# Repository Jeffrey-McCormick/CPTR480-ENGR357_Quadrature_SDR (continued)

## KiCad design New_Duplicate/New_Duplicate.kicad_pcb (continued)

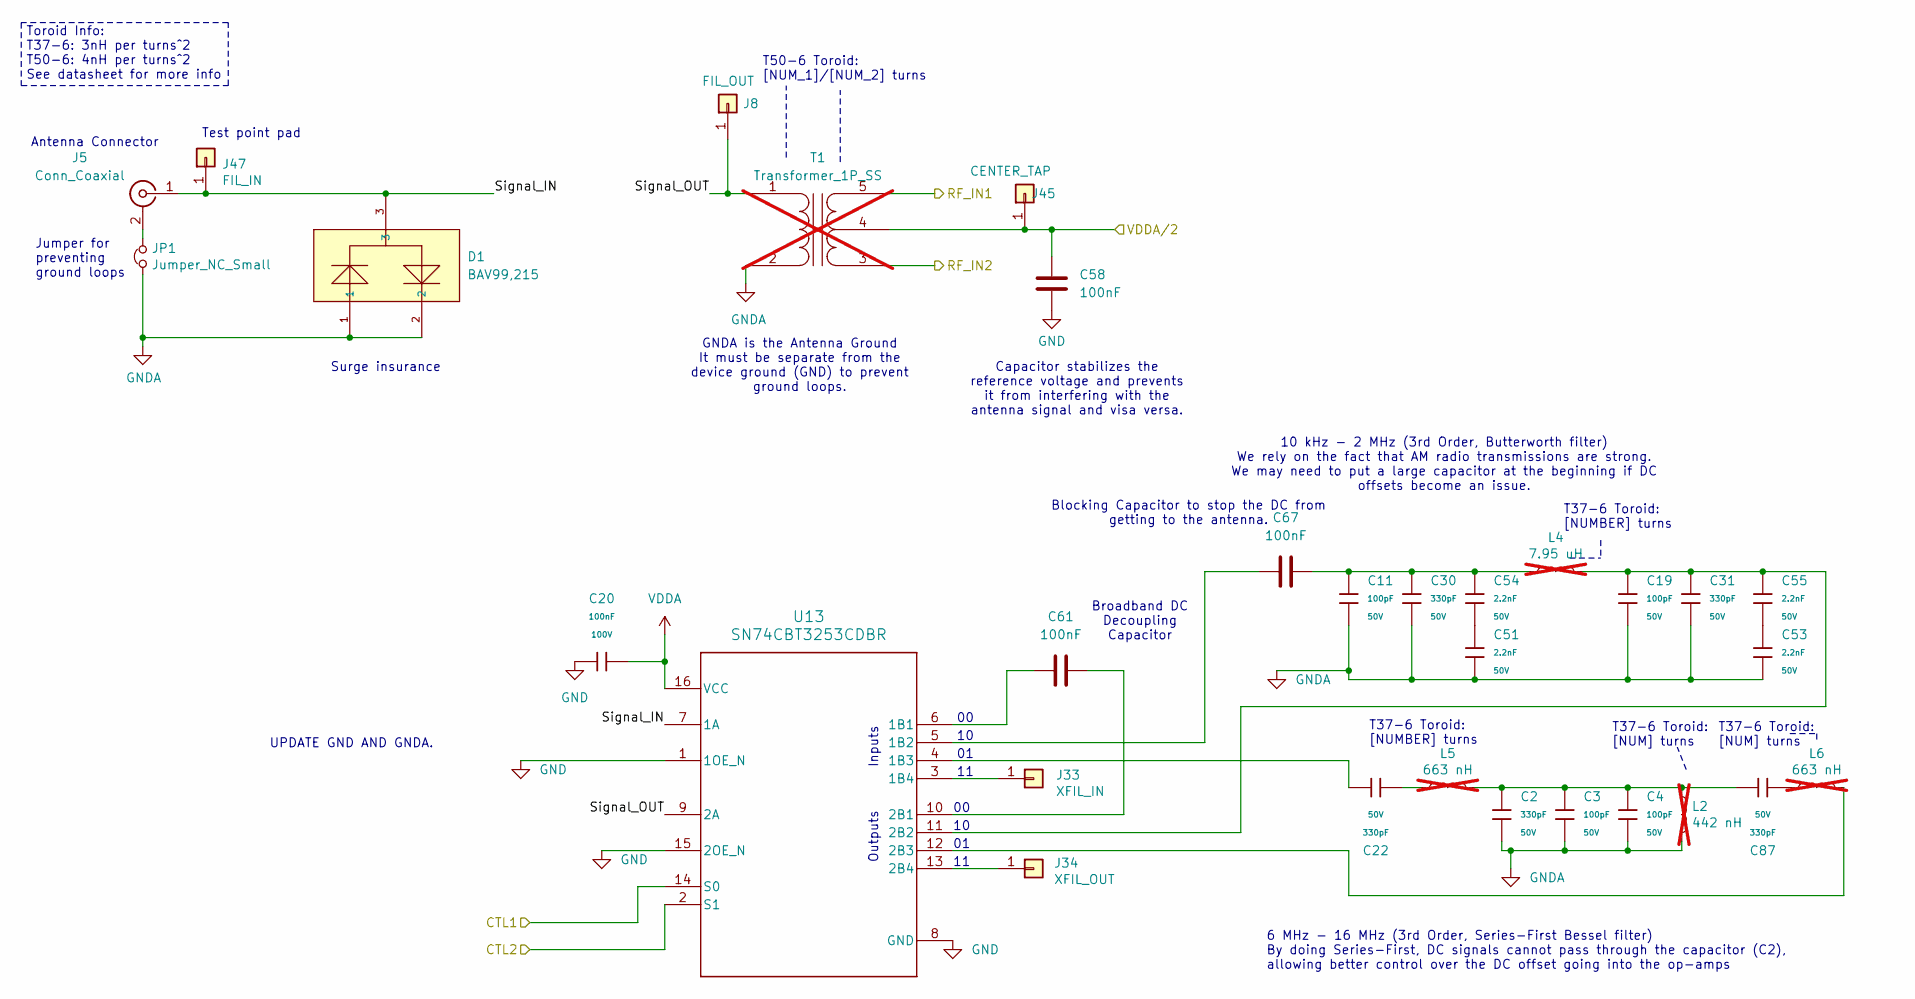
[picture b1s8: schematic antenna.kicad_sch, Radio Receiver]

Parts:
C2, C22, C30, C31, C87: 330pF; C_0603; Voltage Rated 50V; Tolerance ±5%; Part CL10C331JB8NNNC; LCSC C1664
C3, C4, C11, C19: 100pF; C_0402; Voltage Rated 50V; Tolerance ±5%; Part 0402CG101J500NT; LCSC C1546
C20: 100nF; C_0805; Voltage Rated 100V; Tolerance ±10%; Part CL21B104KCFNNNE; LCSC C28233
C51, C53, C54, C55: 2.2nF; C_0805; Voltage Rated 50V; Tolerance ±5%; Part CL21C222JBFNNNE; LCSC C28260
C58, C61, C67: 100nF; C_1206; LCSC C52147198
D1: BAV99,215; SOT-23-3_L3.0-W1.7-P0.95-LS2.9-BR; Reverse Voltage (Vr) 100V; Forward Voltage (Vf@If) 1.25V@150mA; Part BAV99,215; LCSC C2500
J5: Conn_Coaxial; Conn_Coaxial_Frohne
J8: FIL_OUT; PinHeader_1x01_P2.54mm_Vertical
J33: XFIL_IN; PinHeader_1x01_P2.54mm_Vertical
J34: XFIL_OUT; PinHeader_1x01_P2.54mm_Vertical
J45: CENTER_TAP; PinHeader_1x01_P2.54mm_Vertical
J47: FIL_IN; PinHeader_1x01_P2.54mm_Vertical
JP1: Jumper_NC_Small; SolderJumper-2_P1.3mm_Bridged2Bar_RoundedPad1.0x1.5mm
L2: 442 nH; L_Toroid_Vertical_L10.0mm_W5.0mm_P5.08mm; not fitted
L4: 7.95 uH; L_Toroid_Vertical_L13.0mm_W6.5mm_P5.60mm; not fitted
L5, L6: 663 nH; L_Toroid_Vertical_L13.0mm_W6.5mm_P5.60mm; not fitted
T1: Transformer_1P_SS; Transformer_Toroid_Vertical_2Pri_3Sec_T37; not fitted
U13: SN74CBT3253CDBR; DB0016A_N; LCSC C2674583

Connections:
/ADC-24bit/VDDA/2: C58.1, J45.1 (Pin_1_1), T1.4 (SC); also elsewhere on the board
/Antenna/Signal_IN: D1.3, J5.1 (In), J47.1 (Pin_1_1), U13.7 (1A)
/Antenna/Signal_OUT: J8.1 (Pin_1_1), T1.1 (AA), U13.9 (2A)
/CTL1: U13.14 (S0); also elsewhere on the board
/CTL2: U13.2 (S1); also elsewhere on the board
/RF_IN1: T1.5 (SB); also elsewhere on the board
/RF_IN2: T1.3 (SA); also elsewhere on the board
GNDA: C2.2, C3.2, C4.2, C11.2, C19.2, C30.2, C31.2, C51.2, C53.2, D1.1, D1.2, JP1.1, L2.2, T1.2 (AB)
unnamed: C2.1, C3.1, C4.1, C87.1, L2.1, L5.2
unnamed: C11.1, C30.1, C54.1, C67.2, L4.1
unnamed: C22.2, L5.1
unnamed: C51.1, C54.2
unnamed: C53.1, C55.2
unnamed: C87.2, L6.1
unnamed: J5.2 (Ext), JP1.2
unnamed: J33.1 (Pin_1_1), U13.3 (1B4)
unnamed: J34.1 (Pin_1_1), U13.13 (2B4)
unnamed: C61.1, U13.6 (1B1)
unnamed: C67.1, U13.5 (1B2)
unnamed: C22.1, U13.4 (1B3)
unnamed: C61.2, U13.10 (2B1)
unnamed: C19.1, C31.1, C55.1, L4.2, U13.11 (2B2)
unnamed: L6.2, U13.12 (2B3)
VDDA: C20.2, U13.16 (VCC); also elsewhere on the board

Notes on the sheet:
Capacitor stabilizes the reference voltage and prevents it from interfering with the antenna signal and visa versa.
Broadband DC Decoupling Capacitor
T50-6 Toroid: [NUM_1]/[NUM_2] turns
Test point pad
T37-6 Toroid: [NUMBER] turns
Surge insurance
Blocking Capacitor to stop the DC from getting to the antenna.
T37-6 Toroid: [NUM] turns
10 kHz - 2 MHz (3rd Order, Butterworth filter) We rely on the fact that AM radio transmissions are strong. We may need to put a large capacitor at the beginning if DC offsets become an issue.
Jumper for preventing ground loops
Toroid Info: T37-6: 3nH per turns^2 T50-6: 4nH per turns^2 See datasheet for more info
Outputs
T37-6 Toroid: [NUM] turns
UPDATE GND AND GNDA.
GNDA is the Antenna Ground It must be separate from the device ground (GND) to prevent ground loops.
Antenna Connector
6 MHz - 16 MHz (3rd Order, Series-First Bessel filter) By doing Series-First, DC signals cannot pass through the capacitor (C2), allowing better control over the DC offset going into the op-amps
Inputs

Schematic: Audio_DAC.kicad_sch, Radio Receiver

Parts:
C7, C17: 2.2uF; C_0805; Voltage Rated 50V; Tolerance ±10%; Part CL21A225KBQNNNE; LCSC C377773
C10, C41, C45, C46: 10uF; C_CASE-A-3216-18(mm); Tolerance ±10%; Rated Voltage 16V; Part TAJA106K016RNJ; LCSC C7171
C18, C37: 100nF; C_0402; Voltage Rated 50V; Tolerance ±10%; Part CL05B104KB54PNC; LCSC C307331
C42, C43: 2.2nF; C_0805; Voltage Rated 50V; Tolerance ±5%; Part CL21C222JBFNNNE; LCSC C28260
C49, C60, C88: 10uF; C_0805; Voltage Rated 50V; Tolerance ±10%; Part GRM21BR61H106KE43L; LCSC C440198
C50, C57: 100nF; C_0805; Voltage Rated 100V; Tolerance ±10%; Part CL21B104KCFNNNE; LCSC C28233
C59, C68, C85, C86, C89: 100uF; C_CASE-B-3528-21(mm); Tolerance ±10%; Rated Voltage 6.3V; Part TAJB107K006RNJ; LCSC C16133
C64: 1uF; C_0603; Voltage Rated 50V; Tolerance ±10%; Part CL10A105KB8NNNC; LCSC C15849
C66, C84, C96: 100nF; C_1206; LCSC C52147198
FB11, FB12: FB_0805; Current Rating 500mA; Tolerance ±25%; Part GZ2012D601TF; LCSC C1017
J35, J46: 3.5mm_Jack; Jack_3.5mm_CUI_SJ-3523-SMT_Horizontal; LCSC C18594
J38: DAC_FLT; PinHeader_1x01_P2.54mm_Vertical
J40: DAC_FMT; PinHeader_1x01_P2.54mm_Vertical
JP6, JP10: Jumper_2_Bridged; SolderJumper-2_P1.3mm_Bridged_RoundedPad1.0x1.5mm
R6: 47kΩ; R_0603; Overload Voltage (Max) 75V; Tolerance ±1%; Part 0603WAF4702T5E; LCSC C25819
R10, R29: 470Ω; R_0805; Overload Voltage (Max) 150V; Tolerance ±1%; Part 0805W8F4700T5E; LCSC C17710
R28, R43: 10Ω; R_0603; Overload Voltage (Max) 75V; Tolerance ±1%; Part 0603WAF100JT5E; LCSC C22859
R32, R42: 2.2Ω; R_0805; Overload Voltage (Max) 150V; Tolerance ±1%; Part 0805W8F220KT5E; LCSC C17521
R33, R44: 10kΩ; R_0805; Overload Voltage (Max) 150V; Tolerance ±1%; Part 0805W8F1002T5E; LCSC C17414
R45: 6.8kΩ; R_0603; Overload Voltage (Max) 75V; Tolerance ±1%; Part 0603WAF6801T5E; LCSC C23212
R48: 33Ω; R_0805; Overload Voltage (Max) 150V; Tolerance ±1%; Part 0805W8F330JT5E; LCSC C17634
U14: PCM5102A; TSSOP-20_4.4x6.5mm_P0.65mm; LCSC C107671
e3, e4: Groundloop_Insurance; SolderJumper-2_P1.3mm_Bridged_RoundedPad1.0x1.5mm

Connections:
+3.3V: C37.1, C46.1, U14.20 (DVDD); also elsewhere on the board
+3.3VA: R32.1, R42.1; also elsewhere on the board
/Audio DAC/SCK: U14.12 (SCK); also elsewhere on the board
/BCK: U14.13 (BCK); also elsewhere on the board
/LRCK: U14.15 (LRCK); also elsewhere on the board
/MUTE: U14.17 (XSMT); also elsewhere on the board
/SDIN: U14.14 (DIN); also elsewhere on the board
AMP+: C49.2, R6.2; also elsewhere on the board
AMP-: C59.1, C68.1, C85.1, C86.1, C89.1, C96.1; also elsewhere on the board
unnamed: C42.1, C60.1, R29.1, R44.2
unnamed: C43.1, C88.2, R10.2, R33.1
unnamed: C49.1, R33.2, R44.1, R45.2
unnamed: C59.2, C68.2, C85.2, C86.2, C89.2, C96.2, R48.1
unnamed: C60.2, J35.R
unnamed: C64.1, FB11.1, R32.2
unnamed: C88.1, J35.T
unnamed: FB12.1, R42.2
unnamed: J38.1 (Pin_1_1), JP6.2 (B), U14.11 (FLT)
unnamed: J40.1 (Pin_1_1), JP10.1 (A), U14.16 (FMT)
unnamed: J46.R, J46.T, R48.2
unnamed: C10.1, C66.1, FB11.2, U14.8 (AVDD)
unnamed: C17.1, U14.4 (CAPM)
unnamed: C17.2, U14.2 (CAPP)
unnamed: C41.1, C84.1, FB12.2, U14.1 (CPVDD)
unnamed: C18.1, C45.1, U14.18 (LDOO)
unnamed: R10.1, U14.6 (OUTL)
unnamed: R29.2, U14.7 (OUTR)
unnamed: C7.1, U14.5 (VNEG)
unnamed: C50.2, J35.S, R28.1, e3.2 (B)
unnamed: C57.1, e4.1 (A)
unnamed: C57.2, J46.S, R43.1, e4.2 (B)
V_DIV: R6.1; also elsewhere on the board

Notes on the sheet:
PI Filter
Place this charge pump capacitor as close as possible to the DAC to minimize noise radiated from the traces.
Non-inverting amplifier here to drive head phones.
C0G
High impedance loads ONLY (e.g. ACS90 speakers)
500.1uF Bank
OPA1612 HP Low-Noise Amp
Low impedance loads ONLY (e.g. Anker Soundcore Q20)

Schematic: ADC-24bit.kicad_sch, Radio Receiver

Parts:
C16: 10uF; C_0805; Voltage Rated 50V; Tolerance ±10%; Part GRM21BR61H106KE43L; LCSC C440198
C23, C24: 2.2nF; C_0805; Voltage Rated 50V; Tolerance ±5%; Part CL21C222JBFNNNE; LCSC C28260
C25, C28, C44, C98: 10uF; C_CASE-A-3216-18(mm); Tolerance ±10%; Rated Voltage 16V; Part TAJA106K016RNJ; LCSC C7171
C26, C27, C29, C52: 100nF; C_0805; Voltage Rated 100V; Tolerance ±10%; Part CL21B104KCFNNNE; LCSC C28233
C47, C48: 1uF; C_0805; Voltage Rated 50V; Tolerance ±10%; Part CL21B105KBFNNNE; LCSC C28323
C83: 100nF; C_1206; LCSC C52147198
C93, C97: 1uF; C_0603; Voltage Rated 50V; Tolerance ±10%; Part CL10A105KB8NNNC; LCSC C15849
C94, C95: 100nF; C_0402; Voltage Rated 50V; Tolerance ±10%; Part CL05B104KB54PNC; LCSC C307331
FB20, FB21: FB_0805; Current Rating 500mA; Tolerance ±25%; Part GZ2012D601TF; LCSC C1017
J21: SDR Out; Jack_3.5mm_CUI_SJ-3523-SMT_Horizontal; LCSC C18594
J41: V_DIV; PinHeader_1x01_P2.54mm_Vertical
J42: VDDA/2; PinHeader_1x01_P2.54mm_Vertical
JP5: Jumper_2_Bridged; SolderJumper-2_P1.3mm_Bridged_RoundedPad1.0x1.5mm
JP11: Jumper_2_Open; SolderJumper-2_P1.3mm_Open_RoundedPad1.0x1.5mm
R3: 1kΩ; R_0402; Overload Voltage (Max) 50V; Tolerance ±1%; Part 0402WGF1001TCE; LCSC C11702
R5, R52, R53: 22kΩ; R_0805; Overload Voltage (Max) 150V; Tolerance ±1%; Part 0805W8F2202T5E; LCSC C17560
R17, R18: 430Ω; R_0603; Overload Voltage (Max) 75V; Tolerance ±1%; Part 0603WAF4300T5E; LCSC C23170
R19, R20, R21: 33Ω; R_0805; Overload Voltage (Max) 150V; Tolerance ±1%; Part 0805W8F330JT5E; LCSC C17634
R31: 10Ω; R_0603; Overload Voltage (Max) 75V; Tolerance ±1%; Part 0603WAF100JT5E; LCSC C22859
R46: 2.2Ω; R_0805; Overload Voltage (Max) 150V; Tolerance ±1%; Part 0805W8F220KT5E; LCSC C17521
U10: OPA1612AID; D8-M; LCSC C2871441
U12: PCM1808PWR; TSSOP-14_4.4x5mm_P0.65mm; PARTREV B; LCSC C55513
e5: Groundloop_Insurance; SolderJumper-2_P1.3mm_Bridged_RoundedPad1.0x1.5mm

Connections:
+3.3V: C25.1, C26.2, U12.4 (VDD), U12.10 (MD0); also elsewhere on the board
/ADC-24bit/SCKI: U12.6 (SCKI); also elsewhere on the board
/ADC-24bit/VDDA/2: J42.1 (Pin_1_1), R5.2; also elsewhere on the board
/BCKO: R20.2; also elsewhere on the board
/DATA: R19.2; also elsewhere on the board
/FMT: U12.12 (FMT); also elsewhere on the board
/I: C47.2; also elsewhere on the board
/MD1: U12.11 (MD1); also elsewhere on the board
/Q: C48.2; also elsewhere on the board
/WS: R21.2; also elsewhere on the board
AMP+: U10.5 (+); also elsewhere on the board
AMP-: U10.6 (-), U10.7; also elsewhere on the board
unnamed: C47.1, J21.R, R17.1
unnamed: C48.1, J21.T, R18.1
unnamed: C93.1, C94.2, FB21.2, R52.1
unnamed: C97.1, FB20.1, R46.2
unnamed: JP5.2 (B), R3.2
unnamed: C16.1, JP5.1 (A), JP11.2 (B), U10.3 (+)
unnamed: R5.1, U10.1, U10.2 (-)
unnamed: C83.1, C98.1, FB20.2, U10.8 (V+)
unnamed: R20.1, U12.8 (BCK)
unnamed: R19.1, U12.9 (DOUT)
unnamed: R21.1, U12.7 (LRCK)
unnamed: C23.1, R17.2, U12.13 (VINL)
unnamed: C24.1, R18.2, U12.14 (VINR)
unnamed: C27.2, C44.1, R3.1, U12.1 (VREF)
unnamed: C52.2, J21.S, R31.1, e5.2 (B)
VDDA: C28.1, C29.2, FB21.1, R46.1, U12.3 (VCC); also elsewhere on the board
V_DIV: C94.1, C95.2, J41.1 (Pin_1_1), JP11.1 (A), R52.2, R53.1; also elsewhere on the board

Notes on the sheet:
OPA1612 High Performance Low-Noise Amp
GND and GNDA all the same second layer from the top. Follow the new way of making one big ground plane for the second layer and as much ground plane on top and bottom as possible, with the power plane on the third layer.
10 - 45 Ohm resistor "hides" the downstream capacitance from the Op-Amp, ensuring it stays stable.
24.576 MHz osc. (allows 48 kHz or 96 kHz)
BCK (BCKO)
Having the I and Q inputs here eliminates the mismatch between C1 and C4.
SD (DATA)
Second Op Amp and divided voltage go to DAC stage
24 Bit ADC
C0G
Place Audio Jack for Quisk Here
I2S
PI Filter
LRCK (WS)

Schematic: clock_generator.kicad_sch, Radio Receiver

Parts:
C8: 100nF; C_0402; Voltage Rated 50V; Tolerance ±10%; Part CL05B104KB54PNC; LCSC C307331
C56: 10nF; C_0805; Voltage Rated 50V; Tolerance ±10%; Part CL21B103KBANNNC; LCSC C1710
C70, C75: 1uF; C_0603; Voltage Rated 50V; Tolerance ±10%; Part CL10A105KB8NNNC; LCSC C15849
C71, C76, C80: 10uF; C_CASE-A-3216-18(mm); Tolerance ±10%; Rated Voltage 16V; Part TAJA106K016RNJ; LCSC C7171
C72, C77, C78: 100nF; C_1206; LCSC C52147198
FB13, FB15, FB16, FB17: FB_0805; Current Rating 500mA; Tolerance ±25%; Part GZ2012D601TF; LCSC C1017
J9: CLK_1; PinHeader_1x01_P2.54mm_Vertical
J10: CLK_2; PinHeader_1x01_P2.54mm_Vertical
J11: I_LO; PinHeader_1x01_P2.54mm_Vertical
J12: Q_LO; PinHeader_1x01_P2.54mm_Vertical
J24: CLK_0; PinHeader_1x01_P2.54mm_Vertical
JP12: Jumper_2_Open; SolderJumper-2_P1.3mm_Open_RoundedPad1.0x1.5mm
R1, R2: 1kΩ; R_0402; Overload Voltage (Max) 50V; Tolerance ±1%; Part 0402WGF1001TCE; LCSC C11702
R4, R41: 2.2Ω; R_0805; Overload Voltage (Max) 150V; Tolerance ±1%; Part 0805W8F220KT5E; LCSC C17521
R34, R35, R36: 33Ω; R_0805; Overload Voltage (Max) 150V; Tolerance ±1%; Part 0805W8F330JT5E; LCSC C17634
R39, R40: 22Ω; R_0603; Overload Voltage (Max) 75V; Tolerance ±1%; Part 0603WAF220JT5E; LCSC C23345
U5: Si5351A-B-GT; MSOP-10_3x3mm_P0.5mm; LCSC C504891
U6: SN74AC74DR; D14; LCSC C352945
Y1: ASTX-H11-24.576MHZ-T; XTAL_ASTX-H11-24.576MHZ-T; PARTREV 05.13.15; LCSC C1987701

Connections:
+3.3V: R1.1, R2.1; also elsewhere on the board
+3.3VA: C75.1, FB15.1, FB17.1, R4.1, R41.1; also elsewhere on the board
/ADC-24bit/SCKI: R34.1; also elsewhere on the board
/Clock Generator/I_LO: R40.2; also elsewhere on the board
/Clock Generator/Q_LO: R39.1; also elsewhere on the board
/EX_CLK: R36.1; also elsewhere on the board
/OSC_SCL: R1.2, U5.4 (SCL); also elsewhere on the board
/OSC_SDA: R2.2, U5.5 (SDA); also elsewhere on the board
unnamed: C70.1, FB13.1, R41.2
unnamed: FB16.1, R4.2
unnamed: J9.1 (Pin_1_1), U5.9 (CLK1)
unnamed: J10.1 (Pin_1_1), U5.6 (CLK2)
unnamed: J11.1 (Pin_1_1), R40.1, U6.6 (~Q)
unnamed: J12.1 (Pin_1_1), R39.2, U6.2 (D), U6.8 (~Q)
unnamed: J24.1 (Pin_1_1), U5.10 (CLK0), U6.3 (C), U6.11 (C)
unnamed: JP12.1 (A), R36.2
unnamed: JP12.2 (B), R34.2, R35.1, Y1.3 (OUTPUT)
unnamed: C76.1, C77.1, FB15.2, U5.1 (VDD)
unnamed: C78.1, C80.1, FB16.2, U5.7 (VDDO)
unnamed: R35.2, U5.2 (XA)
unnamed: U6.5 (Q), U6.12 (D)
unnamed: C8.1, C71.1, C72.1, FB13.2, U6.1 (~R), U6.4 (~S), U6.10 (~S), U6.13 (~R), U6.14 (VCC)
unnamed: C56.1, FB17.2, Y1.1 (TRI_STATE), Y1.4 (VDD)

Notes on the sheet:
PI Filter
I2C
24.576 MHz
Johnson Counter CLK/4 Circuit using 74AC74
PI Filters
C0G

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
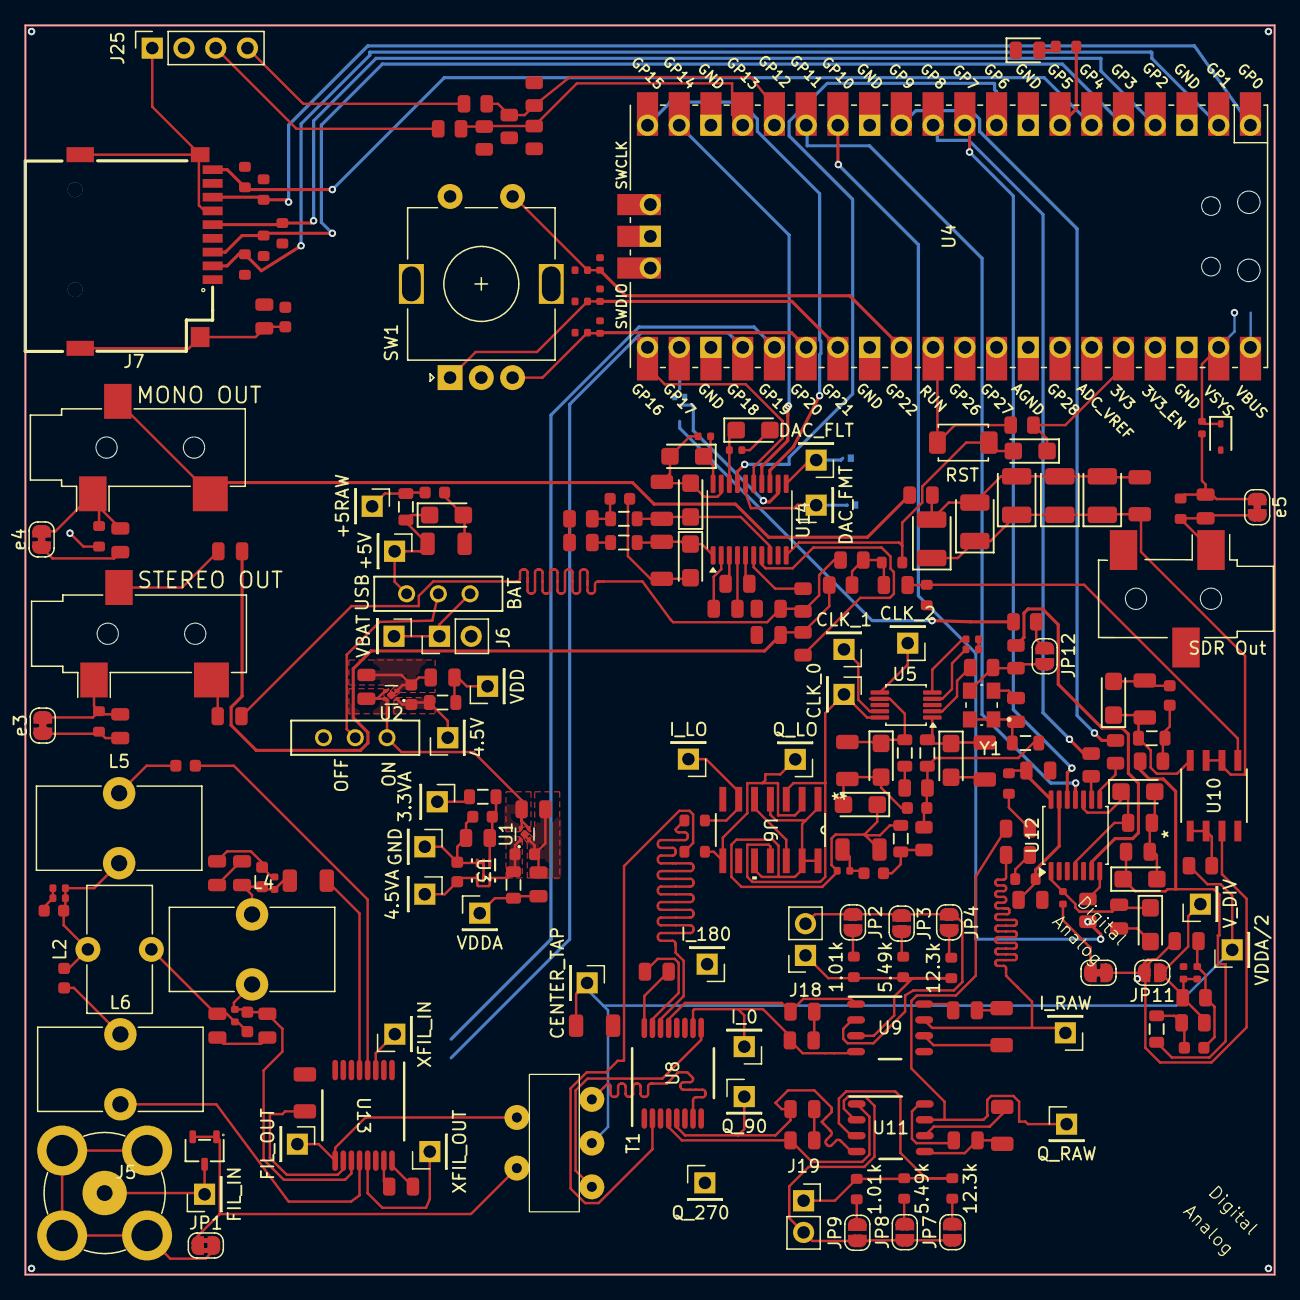
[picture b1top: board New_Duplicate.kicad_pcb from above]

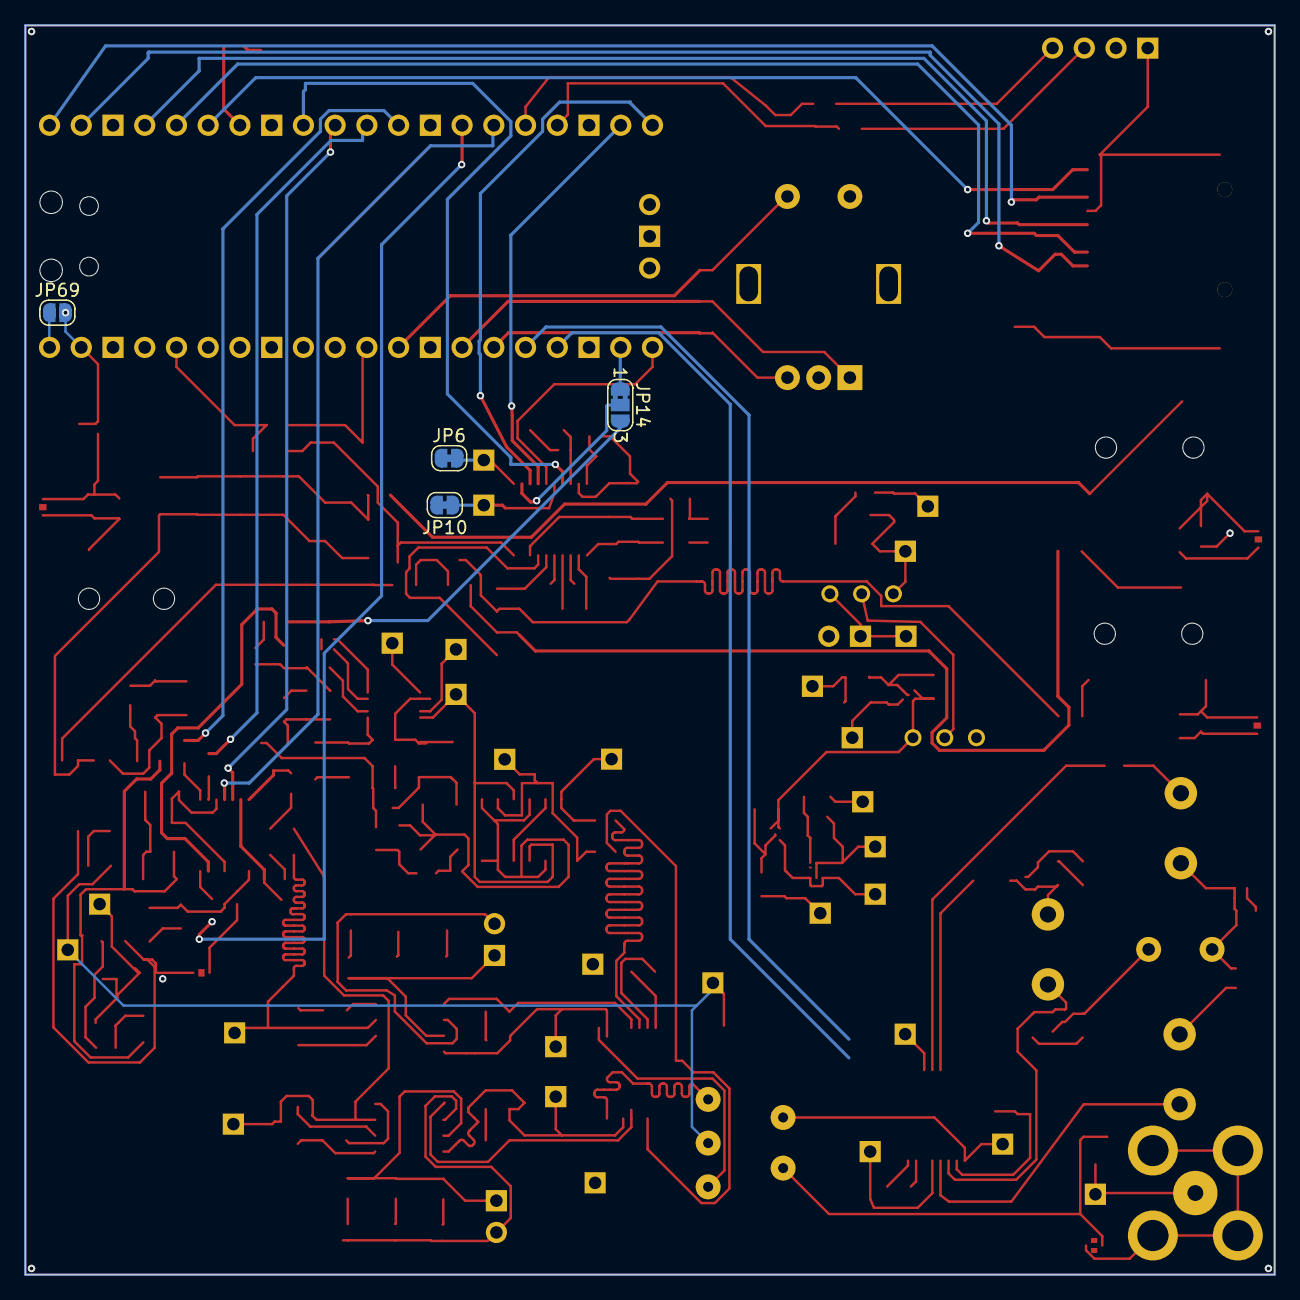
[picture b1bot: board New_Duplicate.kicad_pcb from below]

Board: 4 copper layers, 100.0 x 100.0 mm, 243 parts (4 on the bottom side), 140 nets.

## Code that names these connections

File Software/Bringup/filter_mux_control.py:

"""
Analog Filter MUX Control (CTL1 & CTL2)

Code generated with GitHub Copilot (Claude Haiku 4.5).
Pin configuration and hardware tested by Jeffrey McCormick.

Usage:
  1. Upload this script to your YD-RP2040 via MicroPico
  2. Run it in the REPL (Ctrl+Enter or F5)
  3. Call select_channel(0-3) to select a MUX channel
  
Sets CTL1 (GPIO19) and CTL2 (GPIO18) for 4-channel analog MUX selection
of 1 of 4 filters to be used.
Filter selection:
  0: CTL1=LOW,  CTL2=LOW   (All pass filter)
  1: CTL1=HIGH, CTL2=LOW   (6 MHz - 16 MHz, 3rd Order, Series-First Bessel filter)
  2: CTL1=LOW,  CTL2=HIGH  (10 kHz - 2 MHz, 3rd Order, Butterworth filter)
  3: CTL1=HIGH, CTL2=HIGH  (External Filter - XFIL)
"""

from machine import Pin
import time

# Initialize control pins
CTL1 = Pin(19, Pin.OUT)  # CTL1 line
CTL2 = Pin(18, Pin.OUT)  # CTL2 line


def select_channel(channel):
    """
    Select a MUX channel (0-3).
    
    Filter selection:
    0: 00 (All pass filter)
    1: 01 (BPF)
    2: 10 (LPF)
    3: 11 (XFIL)
    """
    if channel == 0:
        CTL1.off()   # *** CTL1 set LOW ***
        CTL2.off()   # *** CTL2 set LOW ***
    elif channel == 1:
        CTL1.on()    # *** CTL1 set HIGH ***
        CTL2.off()   # *** CTL2 set LOW ***
    elif channel == 2:
        CTL1.off()   # *** CTL1 set LOW ***
        CTL2.on()    # *** CTL2 set HIGH ***
    elif channel == 3:
        CTL1.on()    # *** CTL1 set HIGH ***
        CTL2.on()    # *** CTL2 set HIGH ***
    else:
        print("Invalid channel. Use 0-3.")




# Example: Cycle through all channels
if __name__ == "__main__":
    select_channel(0)

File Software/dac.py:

"""
DAC code
"""
from machine import I2S, Pin
import time


class DAC:
    def __init__(
        self,
        bck_pin=15,
        ws_pin=16,
        data_pin=14,
        mute_pin=6,
        mclk_pin=17,
        i2s_id=0,
        sample_rate=44100,
        bits=16,
        buffer_size=40000,
        nonblocking=True,
    ):
        """
        Initializes the I2S interface for the PCM5102A.
        """
        self.bck_pin = bck_pin
        self.ws_pin = ws_pin
        self.data_pin = data_pin
        self.mclk_pin = mclk_pin
        self.i2s_id = i2s_id
        self.sample_rate = sample_rate
        self.bits = bits
        self.buffer_size = buffer_size
        self.nonblocking = nonblocking
        self.i2s = None
        self._drain_handler = None

        self.mclk = None
        if self.mclk_pin is not None:
            from machine import PWM
            self.mclk = PWM(Pin(self.mclk_pin))
            self.mclk.freq(self.sample_rate * 256)
            self.mclk.duty_u16(32768)

        self.mute_control = None
        if mute_pin is not None:
            self.mute_control = Pin(mute_pin, Pin.OUT)
            self.mute()

        self.set_stereo()

    def set_drain_handler(self, handler):
        """handler() is called when the I2S ring has space for more audio."""
        self._drain_handler = handler

    def _on_i2s_irq(self, i2s):
        if self._drain_handler:
            self._drain_handler()

    def mute(self):
        """Pulls the XSMT pin LOW to soft-mute the DAC output."""
        if self.mute_control:
            self.mute_control.value(0)

    def unmute(self):
        """Pulls the XSMT pin HIGH to unmute the DAC output."""
        if self.mute_control:
            self.mute_control.value(1)

    def _configure_i2s(self, format_mode):
        """Internal helper to set up or re-initialize the I2S hardware."""
        if self.i2s:
            self.i2s.deinit()

        self.i2s = I2S(
            self.i2s_id,
            sck=Pin(self.bck_pin),
            ws=Pin(self.ws_pin),
            sd=Pin(self.data_pin),
            mode=I2S.TX,
            bits=self.bits,
            format=format_mode,
            rate=self.sample_rate,
            ibuf=self.buffer_size,
        )

        if self.nonblocking:
            self.i2s.irq(self._on_i2s_irq)
        else:
            self.i2s.irq(None)

    def set_mono(self):
        """Configures the I2S stream for Mono (Pico duplicates L/R internally)."""
        self._configure_i2s(I2S.MONO)
        print(f"PCM5102A configured for Dual-Mono at {self.sample_rate}Hz")

    def set_stereo(self):
        """Configures the I2S stream for true Stereo output."""
        self._configure_i2s(I2S.STEREO)
        mode = "non-blocking" if self.nonblocking else "blocking"
        print(f"PCM5102A configured for Stereo at {self.sample_rate}Hz ({mode})")

    def write(self, audio_buffer, length=None):
        """
        Write audio to I2S.
        Non-blocking: returns bytes accepted immediately (may be partial).
        Blocking: loops until the full chunk is queued.
        """
        if not self.i2s:
            return 0

        view = memoryview(audio_buffer)
        if length is not None:
            view = view[:length]

        if self.nonblocking:
            return self.i2s.write(view)

        offset = 0
        total = len(view)
        while offset < total:
            offset += self.i2s.write(view[offset:])
        return offset

    def write_buffer(self, audio_buffer, length=None):
        """Alias for write(); kept for older callers."""
        return self.write(audio_buffer, length)

    def close(self):
        """Mutes the DAC and safely shuts down the I2S peripheral."""
        self._drain_handler = None
        if self.i2s:
            self.i2s.irq(None)
        self.mute()
        time.sleep_ms(20)
        if self.i2s:
            self.i2s.deinit()


if __name__ == "__main__":
    import struct
    import math

    dac = DAC(nonblocking=False)
    dac.unmute()

    sample_rate = 44100
    freq = 440
    num_samples = sample_rate
    buf = bytearray(num_samples * 4)

    for i in range(num_samples):
        val = int(32767 * math.sin(2 * math.pi * freq * i / sample_rate))
        struct.pack_into("<hh", buf, i * 4, val, val)

    dac.write_buffer(buf)

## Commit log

2026-04-20 Added KiCAD files and References to parts and design resources.
2026-04-20 Added KiCAD files and references to part resources
2026-04-20 This is for git push
2026-04-20 slight updates to the KiCad files
2026-04-20 Hopefully the .gitignore works here too.
2026-04-20 Removed test.md
2026-04-20 Removed open temp file
2026-04-21 Enhanced .gitignore for KiCad version control and other files
    Updated .gitignore to track Core KiCad files and ignore user-specific settings, autosave files, lock files, plot outputs, 3D artifacts, IDE/editor configurations, OS junk, and Python cache. Product r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
2026-04-21 Stop tracking .history directory
2026-04-21 Propogated Title Block Fields
2026-04-21 Added basic antenna and bandpass filter schematic.
2026-04-21 Added Tayloe Detector MUX symbol and footprint
2026-04-22 Added Bibliography entry
2026-04-23 Add reference to bibliography.
2026-04-24 Added Daniel Mendoza's changes to KiCAD files.
2026-04-28 Added sources of what has been done before.
2026-04-29 Created LTSpice folder.
2026-04-29 Added switchable antenna filters and photos.
2026-04-29 Added footprints
2026-04-29 Schematic connection edits
2026-04-30 Schematic edits power and signal systems
2026-04-30 Simulation for the Low Pass Filter
2026-04-30 Added bibliography source and schematic edits
2026-04-30 Updated Band-pass filter calculation picture
2026-04-30 This is a folder test
2026-04-30 Simulation files added to the LTSpice_Simulations folder and removed unnecessary files
2026-04-30 High Pass filter added
2026-05-01 Removed unnecessary files
2026-05-01 Changed Low pass filter and added screenshots of simulations into the /Pictures folder
2026-05-01 Added reference voltage stability by buffer amp
2026-05-01 Isolated filter switching MUX from digital control
2026-05-02 Added DAC and shaft angle encoder
2026-05-04 Added digital power regulator
2026-05-05 Integrated signal path modules
2026-05-05 Adjusted RF filters for basic component values
2026-05-05 Adjusted values for the LP and BP filters in the LTspice simulations
2026-05-05 Finalized Pico connections and added indicator LEDs
2026-05-06 Added transformer footprint and datasheet
2026-05-06 Swapped voltage regulator to output 4.5V
2026-05-06 Corrected mono to headphones
2026-05-06 temp files
2026-05-06 Added the bnc connector footprint provided by dr Frohne
2026-05-07 Created low mono, high stereo impedance DAC audio outlets
2026-05-07 Added MicroSD card and verified footprints
2026-05-07 Updated footprints
2026-05-07 Started PCB
2026-05-07 Edited PCB Power
2026-05-08 Created duplicate to work parallel without merge conflicts
2026-05-08 Added comment
2026-05-08 Arranged power components on PCB
2026-05-08 Fixed the clock and johnson counter
2026-05-08 Arranged antenna and mixer components on PCB
2026-05-08 Added pico and OLED arrangement to PCB
2026-05-08 ADC finished
2026-05-08 Started adding traces
2026-05-08 Continue on layout of PCB
2026-05-08 Deleted the duplicate
2026-05-08 Added traces for mixer and fixed placing
2026-05-08 Placed ADC and DAC onto the PCB layout
2026-05-08 Laid out all components to fit on PCB
2026-05-08 tracing more things
2026-05-08 Added netclasses for all the critical trace types
2026-05-08 New_Duplicate is the new copy working with traces Not everything on the right diagonal is connected
2026-05-10 More tracing done. Not completly finished.
2026-05-10 More Tracing
2026-05-12 small wire connections
2026-05-12 trace...
2026-05-13 trace to trace
2026-05-14 Routed antenna and isolated GNDA
2026-05-14 Resolved non-connection related DRC errors and warnings
2026-05-14 back copper tracing for raspberry pi done
2026-05-15 Finished routing master copy and added GND and PWR planes with vias
2026-05-15 Corrected footprints saved to Reciever_Parts.pretty
2026-05-15 Resolved all DRC errors and warnings
2026-05-16 Finalized board layout
2026-05-16 Create Radio_Receiver_1.0.0 production files
2026-05-16 Corrected stereo and mono audio jacks' footprints
2026-05-16 Added rotation offsets for JLCPCB order
2026-05-16 Added rotation offset to U8
2026-06-03 Added Turn and Core type values to the hand-wound inductors and transformer
2026-06-05 Added Micropython files for board bring-up testing
2026-06-05 test/code driver changes
2026-06-05 menu
2026-06-05 restored rotary_encoder from test values
2026-06-07 sd read and stream init
2026-06-07 main and menu files added
2026-06-07 added print a and b value print to rotary encoder
2026-06-07 prototype playback controller
2026-06-08 2 core setup
2026-06-09 dac.py driver added
2026-06-09 updated AudioStreamer by changing _audio_thread_worker func
2026-06-09 dac_test
2026-06-10 update menu code to be extensible
2026-06-10 playback controller v1
2026-06-10 dac testing
2026-06-10 ahhhhh
2026-06-10 merge
2026-06-10 it kinda works
2026-06-10 something something
2026-06-10 something might be fixed
2026-06-10 asyncio
2026-06-10 readme
2026-06-10 ui works!!!!
2026-06-10 readme updates
2026-06-10 video
2026-06-10 cleanup ladies and gents
2026-06-10 readme edits
2026-06-10 Enhance RF Front-End section in README
    boom
2026-06-10 added image for johnson counter
2026-06-10 about to present
2026-06-10 calc
